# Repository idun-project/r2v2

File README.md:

## R2V2 - Dual-video switcher & converter for the Commodore 128

This is an open-source project that aims to improve the quality, flexibility, and convenience of the dual-video outputs of the Commodore 128.

In the normal configuration, the C128 has two independent video outputs for the VDC (80-column mode) and the VIC-II (40-column mode) displays. Each display requires its own cable going to its own specific type of monitor input, with the ideal being RGBI input for the 80col display and S-video for the 40col display. You can use two monitors, or you can use a retro monitor (e.g. Commodore 1084) that is manually switchable between two inputs.

With R2V2 installed in a C128, a single port, cable, and monitor input is used for BOTH display modes AND the display mode is switchable using the keyboard or with software control. If you also have the [idun-cartridge](https://github.com/idun-project/idun-cartridge), its software will be able to switch the displays automatically.

### Components

VDC Enhancer (8568) front

VDC Enhancer (8563) back

R2V2 requires two small PCBs installed internally. One sits under the VDC chip, and can optionally include 64KB video RAM expanasion. There are versions for the MOS8563 and the MOS8568 (for C128-DCR). The second PCB installed is from the breakable PCB pictured and is either:

1. An RF modulator replacement, which enhances the 8-pin DIN monitor port plus adds composite monitor and stereo audio outputs (supports 2 SIDs). It can also support switchable **HDMI OUT** from the composite port! (Requires additional components)
2. A modification for the DB-9 monitor port, which outputs analog RGB (rather than RGBI) and can also be used for switchable **HDMI OUT**.

### Status

This is an open-source project still in the R&D phase. It is not fully baked, and you should not try to build it _unless you want to contribute to the testing/debugging effort_.

- [x] Prototype PCBs manufactured
    - [x] MOS8568 VDC enhancer
    - [x] MOS8563 VDC enhancer
    - [x] analog board
- [ ] Prototype PCBs assembled
    - [ ] MOS8568 VDC enhancer
    - [ ] MOS8563 VDC enhancer w/o SRAM
    - [ ] MOS8563 VDC enhancer w/ SRAM
    - [ ] RF modulator replacement
    - [ ] DB-9 mod
- [ ] Testing
    - [ ] MOS8568+RF mod S-vid, composite, audio
    - [ ] MOS8563+RF mod S-vid, composite, audio
    - [ ] MOS8563+SRAM
    - [ ] MOS8563+RF mod LumaCode, mono-80c to RGBtoHDMI
    - [ ] MOS8568+DB-9 mod analog RGB
    - [ ] MOS8568+DB-9 mod LumaCode, color-80c to RGBtoHDMI
    - [ ] MOS8563+DB-9 mod LumaCode, color-80c to RGBtoHDMI

### Configurations

Many different configurations are possible, and depends on the kind of monitor you want to use, be it a retro CRT, modern monitor with analog input, or HDMI.

#### For analog monitor inputs

If you intend to use a monitor that supports S-video, you should be able to get good quality color output for both 80col and 40col display modes. Install the VDC enhancer compatible to your system and the RF modulator replacement, then connect the DIN monitor port to your display. You can use the audio on the DIN port, or plug in to the 3.5mm headphone jack.

If you intend to use a monitor that supports composite, you can get decent color 40col and monochrome 80col from the output on the RCA jack. Install the VDC enhancer and the RF modulator replacement, then connect the composite output to your display. Most likely, you will want to use the 3.5mm heahphone jack for audio.

It is possible to install both the RF modulator replacement and the DB-9 mod. If you do this, then you'll have analog RGB (both RGBS and RGBHV) on the DB-9, and that might be what you want for some monitors (e.g. SCART input). You'll have to work out your own switching between displays using this configuration.

#### For digital HDMI monitors

For the absolute best picture quality on modern displays, the R2V2 is combined with the [VIC-II LumaCode](https://github.com/c0pperdragon/LumaCode/wiki/VICIIdizer128-(for-the-C128)) enhancement and an external [RGBtoHDMI](https://github.com/hoglet67/RGBtoHDMI/wiki) video converter/upscaler.

There is a simpler version of the RGBtoHDMI designed by "C0pperdragon" that handles only LumaCode and monochrome video. This version can be used with the composite output on the RF modulator replacement. You will get color 40col and monochrome 80col display modes from a single HDMI input.

If you want the best HDMI experience with color 80col, then you'll need the more sophisticated RGBtoHDMI converter that handles both LumaCode and RGBS. This version connects with a custom cable to the DB-9 port and uses LumaCode for 40col mode and RGBS for 80col mode.

_NOTE_: A firmware patch and profile for the RGBtoHDMI is being developed so that it will automatically switch display modes as your C128 switches between 40/80col modes.

#### 64KB video RAM

The C128-DCR uses a MOS8568 VDC and came with 64KB of VRAM. Just use the MOS8568 version VDC enhancer and you're all set.

Other models of the C128 use a MOS8563 VDC and came with 16KB of VRAM. You must use the MOS8563 version VDC enhancer, and you can _optionally_ install 2 chips on the back of the PCB to upgrade to 64KB of VRAM.

### Build Instructions

TO BE CONTINUED...

### Installation Instructions

TO BE CONTINUED...

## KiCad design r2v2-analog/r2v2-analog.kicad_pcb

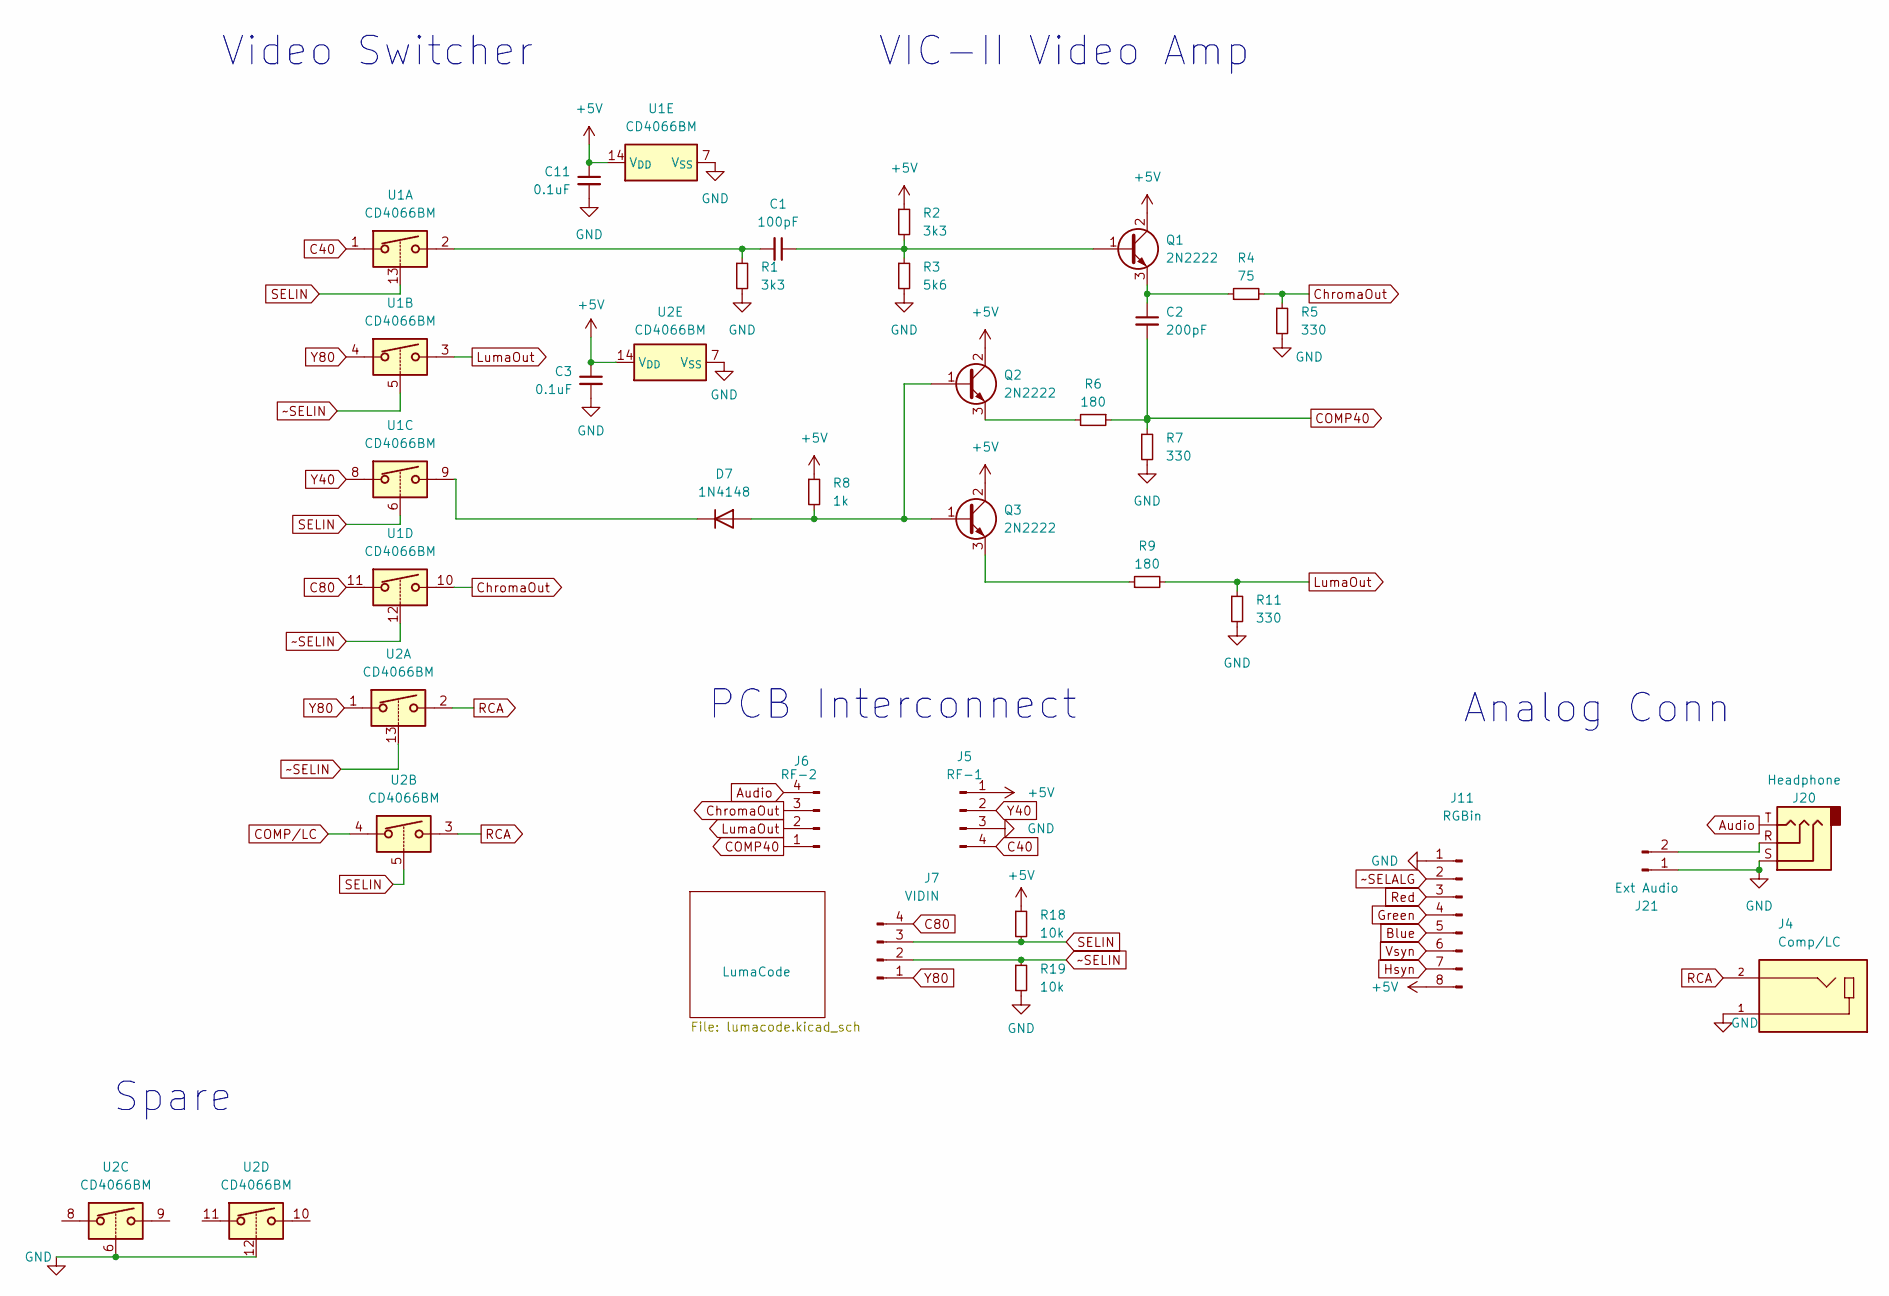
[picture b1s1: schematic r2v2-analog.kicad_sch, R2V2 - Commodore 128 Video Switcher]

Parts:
C1: 100pF; C_1206_3216Metric
C2: 200pF; C_1206_3216Metric
C3, C11: 0.1uF; C_1206_3216Metric
D7: 1N4148; D_SOD-123
J4: Comp/LC; CUI_RCJ-044; PARTREV 1.02
J5: RF-1; PinHeader_1x04_P2.54mm_Vertical
J6: RF-2; PinHeader_1x04_P2.54mm_Vertical
J7: VIDIN; PinHeader_1x04_P2.54mm_Vertical
J11: RGBin; PinHeader_2x04_P2.54mm_Vertical
J20: Headphone; Jack_3.5mm_CUI_SJ1-3523N_Horizontal
J21: Ext Audio; PinHeader_1x02_P2.54mm_Vertical
Q1, Q2, Q3: 2N2222; TO-92
R1, R2: 3k3; R_1206_3216Metric
R3: 5k6; R_1206_3216Metric
R4: 75; R_1206_3216Metric
R5, R7, R11: 330; R_1206_3216Metric
R6, R9: 180; R_1206_3216Metric
R8: 1k; R_1206_3216Metric
R18, R19: 10k; R_1206_3216Metric
U1, U2: CD4066BM; SO-14_3.9x8.65mm_P1.27mm

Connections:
+5V: C3.1, C11.1, J5.1, J11.8, Q1.2 (C), Q2.2 (C), Q3.2 (C), R2.1, R8.1, R18.1, U1.14 (V_{DD}), U2.14 (V_{DD}); also elsewhere on the board
Audio: J6.4, J20.T
Blue: J11.5; also elsewhere on the board
C40: J5.4, U1.1
C80: J7.4, U1.11
COMP40: C2.2, J6.1, R6.1, R7.1; also elsewhere on the board
COMP/LC: U2.4; also elsewhere on the board
ChromaOut: J6.3, R4.2, R5.1, U1.10
GND: C3.2, C11.2, J4.1, J5.3, J11.1, J20.S, J21.1, R1.2, R3.2, R5.2, R7.2, R11.2, R19.2, U1.7 (V_{SS}), U2.6, U2.7 (V_{SS}), U2.12; also elsewhere on the board
Green: J11.4; also elsewhere on the board
Hsyn: J11.7; also elsewhere on the board
LumaOut: J6.2, R9.2, R11.1, U1.3
unnamed: C1.2, R1.1, U1.2
unnamed: D7.2 (A), Q2.1 (B), Q3.1 (B), R8.2
unnamed: D7.1 (K), U1.9
unnamed: J20.R, J21.2
unnamed: C1.1, Q1.1 (B), R2.2, R3.1
unnamed: C2.1, Q1.3 (E), R4.1
unnamed: Q2.3 (E), R6.2
unnamed: Q3.3 (E), R9.1
RCA: J4.2, U2.2, U2.3
Red: J11.3; also elsewhere on the board
SELIN: J7.3, R18.2, U1.6, U1.13, U2.5
Vsyn: J11.6; also elsewhere on the board
Y40: J5.2, U1.8
Y80: J7.1, U1.4, U2.1
~SELALG: J11.2; also elsewhere on the board
~SELIN: J7.2, R19.1, U1.5, U1.12, U2.13

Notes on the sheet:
Spare
VIC-II Video Amp
Video Switcher
Analog Conn
PCB Interconnect

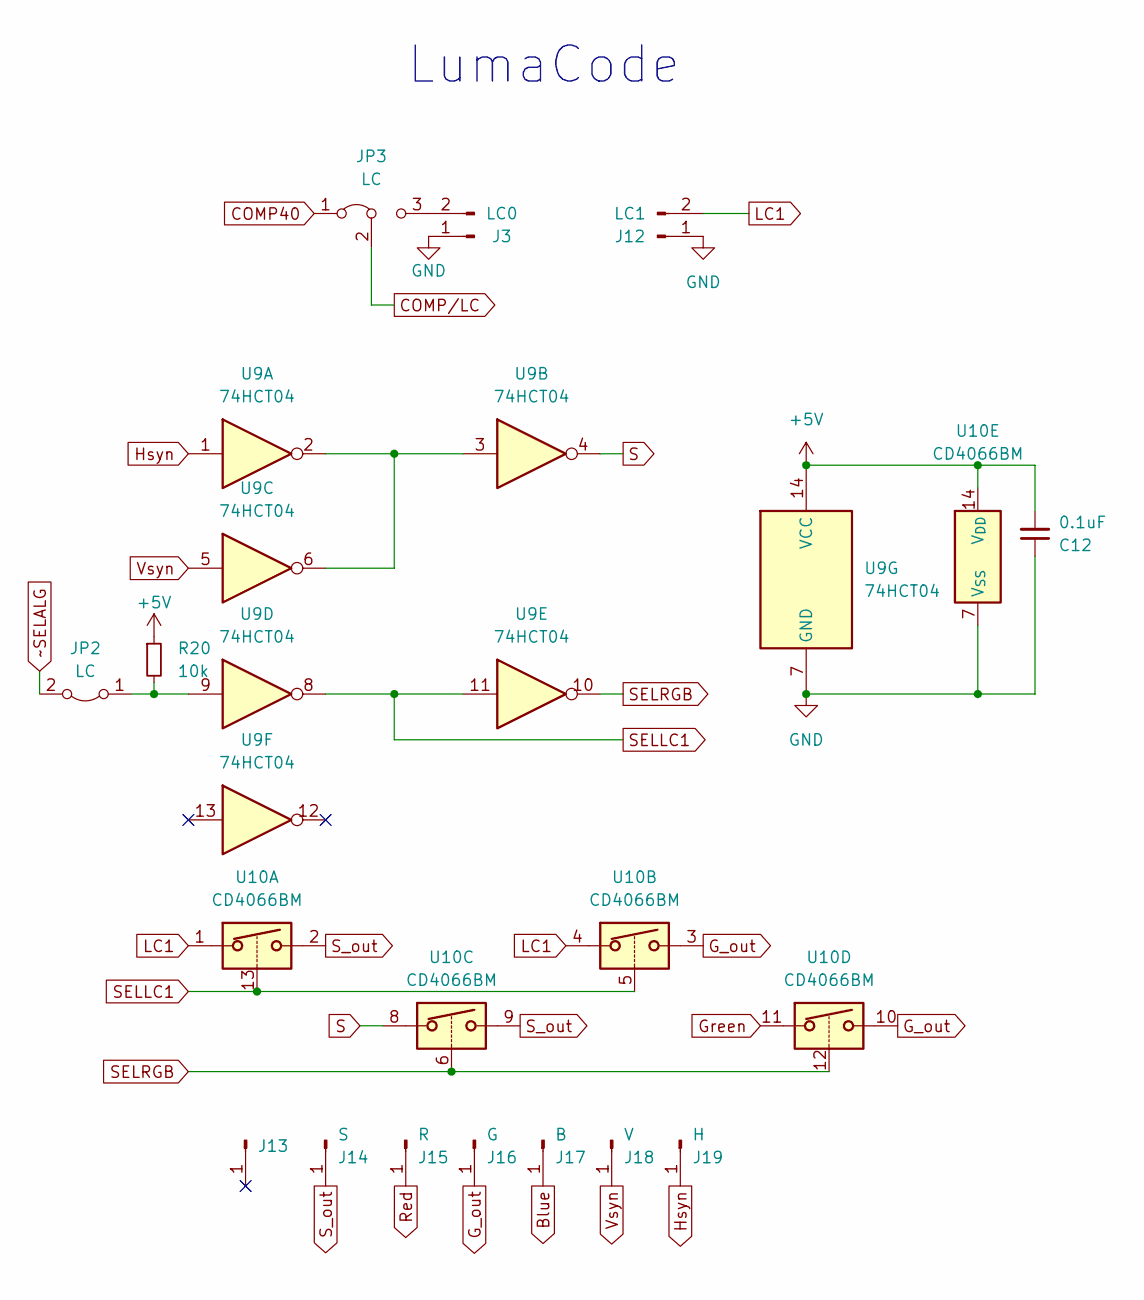
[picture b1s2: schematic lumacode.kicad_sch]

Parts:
C12: 0.1uF; C_1206_3216Metric
J3: LC0; PinHeader_1x02_P2.54mm_Vertical
J12: LC1; PinHeader_1x02_P2.54mm_Vertical
J13: PinHeader_1x01_P2.54mm_Vertical
J14: S; PinHeader_1x01_P2.54mm_Vertical
J15: R; PinHeader_1x01_P2.54mm_Vertical
J16: G; PinHeader_1x01_P2.54mm_Vertical
J17: B; PinHeader_1x01_P2.54mm_Vertical
J18: V; PinHeader_1x01_P2.54mm_Vertical
J19: H; PinHeader_1x01_P2.54mm_Vertical
JP2: LC; PinHeader_1x02_P1.27mm_Vertical
JP3: LC; PinHeader_1x03_P1.27mm_Vertical
R20: 10k; R_1206_3216Metric
U9: 74HCT04; SO-14_3.9x8.65mm_P1.27mm
U10: CD4066BM; SO-14_3.9x8.65mm_P1.27mm

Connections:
+5V: C12.2, R20.1, U9.14 (VCC), U10.14 (V_{DD}); also elsewhere on the board
Blue: J17.1; also elsewhere on the board
COMP40: JP3.1 (A); also elsewhere on the board
COMP/LC: JP3.2 (C); also elsewhere on the board
GND: C12.1, J3.1, J12.1, U9.7 (GND), U10.7 (V_{SS}); also elsewhere on the board
G_out: J16.1, U10.3, U10.10
Green: U10.11; also elsewhere on the board
Hsyn: J19.1, U9.1; also elsewhere on the board
LC1: J12.2, U10.1, U10.4
unnamed: J3.2, JP3.3 (B)
unnamed: JP2.1 (A), R20.2, U9.9
unnamed: U9.2, U9.3, U9.6
Red: J15.1; also elsewhere on the board
S: U9.4, U10.8
SELLC1: U9.8, U9.11, U10.5, U10.13
SELRGB: U9.10, U10.6, U10.12
S_out: J14.1, U10.2, U10.9
Vsyn: J18.1, U9.5; also elsewhere on the board
~SELALG: JP2.2 (B); also elsewhere on the board

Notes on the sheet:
LumaCode

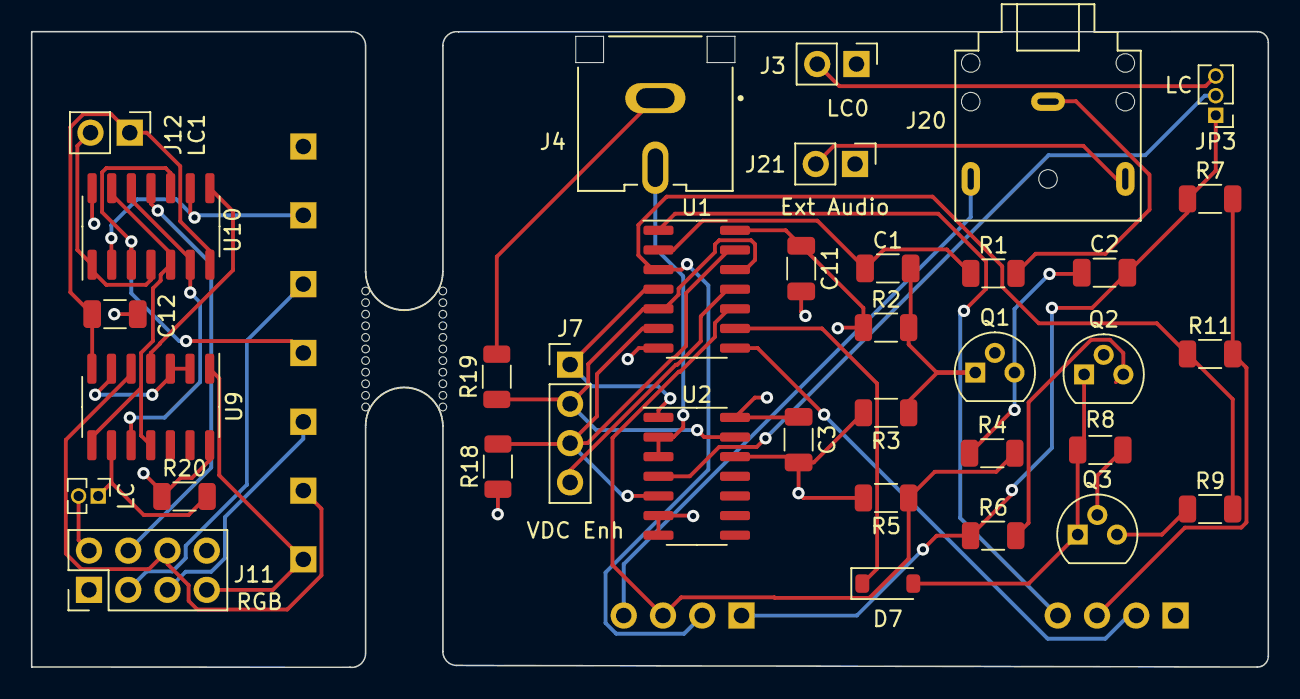
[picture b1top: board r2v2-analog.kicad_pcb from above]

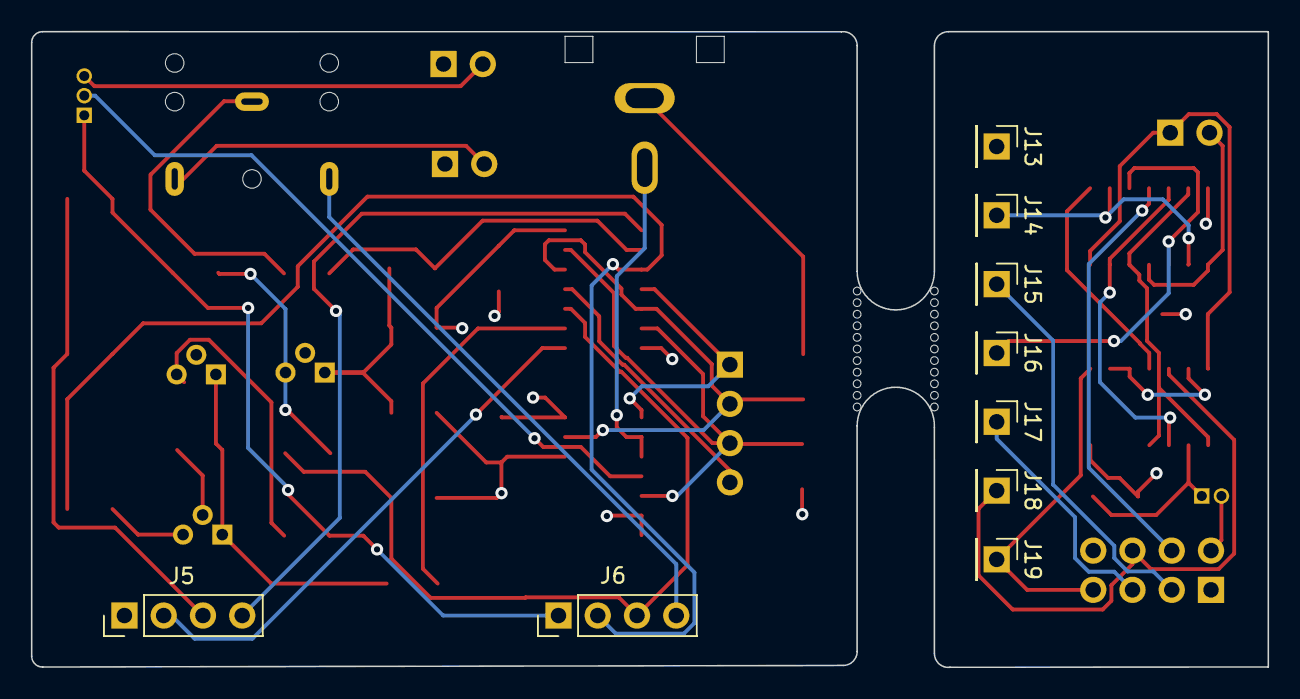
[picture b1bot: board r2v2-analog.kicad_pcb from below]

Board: 4 copper layers, 80.0 x 41.1 mm, 45 parts (9 on the bottom side), 37 nets.

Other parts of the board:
mouse-bite-5mm-slot: VAL**; mouse-bite-5mm-slot

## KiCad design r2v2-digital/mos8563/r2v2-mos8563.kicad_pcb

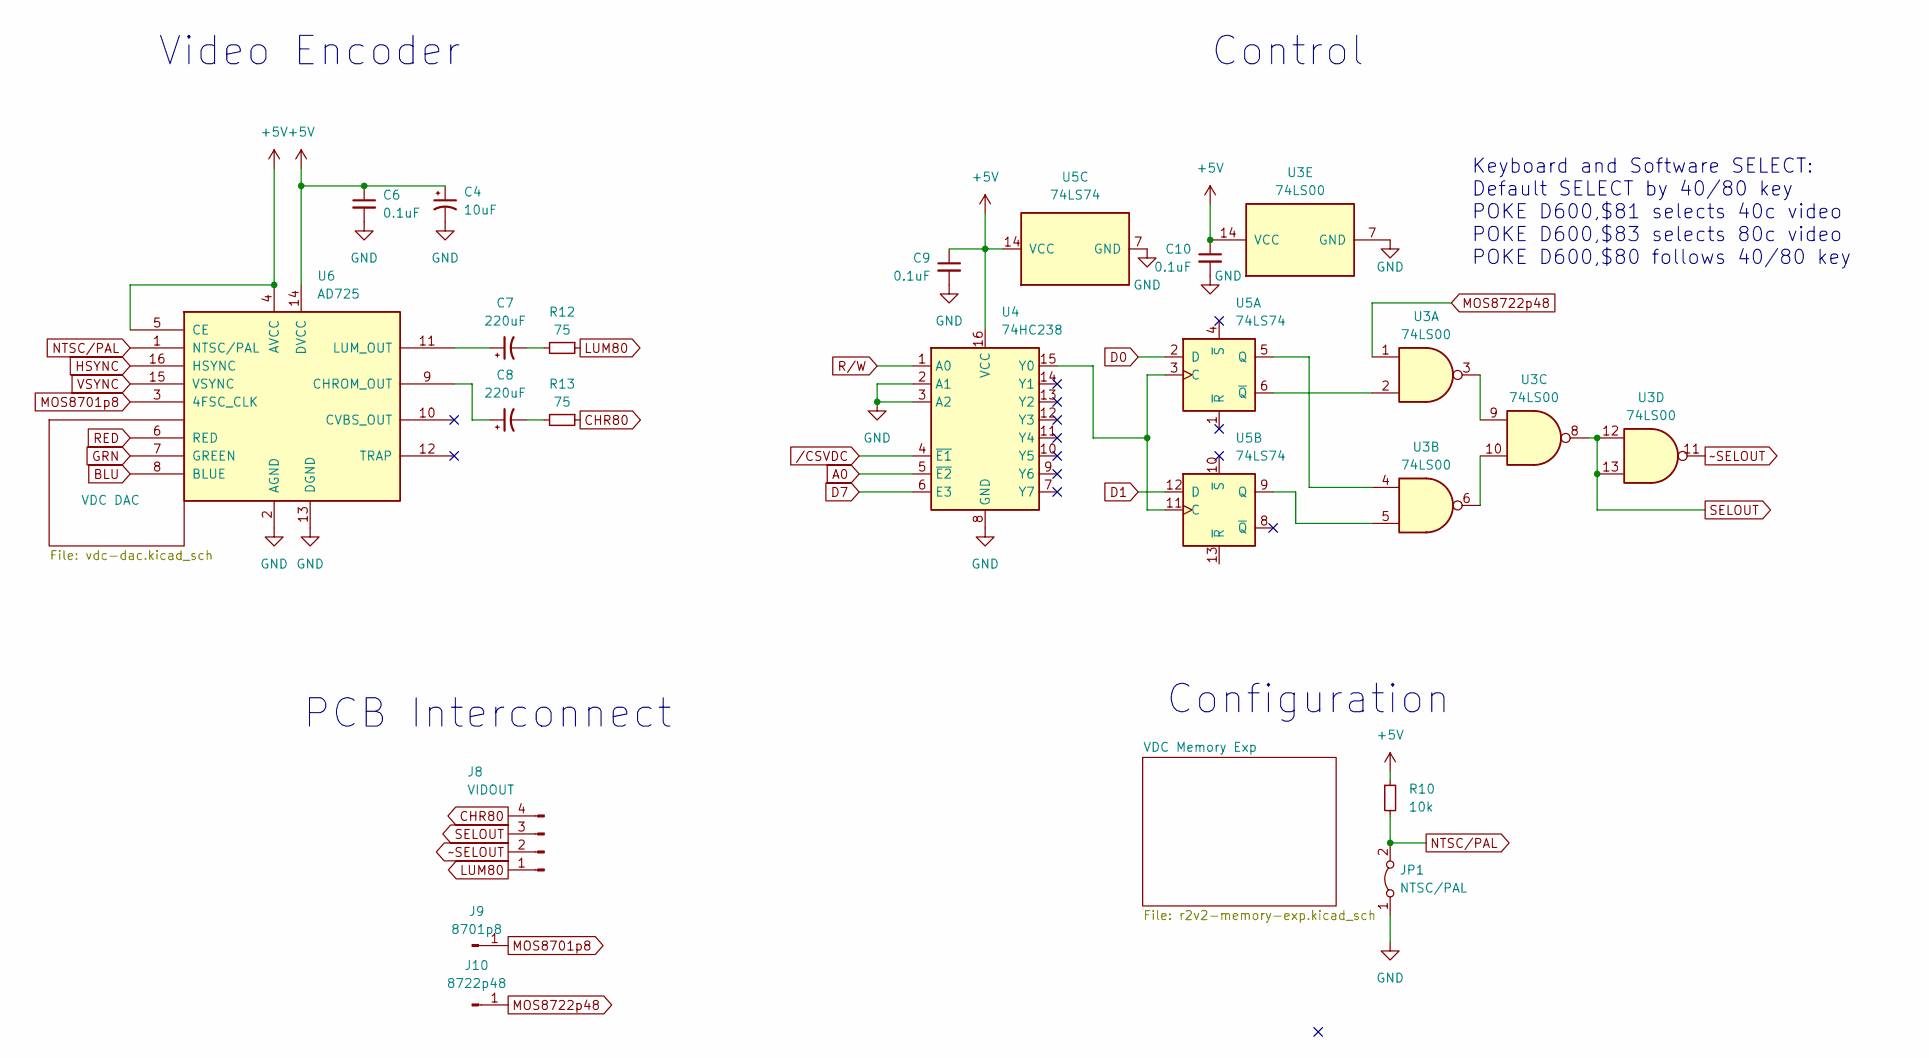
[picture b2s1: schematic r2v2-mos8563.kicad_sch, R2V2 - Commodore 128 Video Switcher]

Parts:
C4: 10uF; C_1206_3216Metric
C6, C9, C10: 0.1uF; C_1206_3216Metric
C7, C8: 220uF; C_1206_3216Metric
J8: VIDOUT; PinHeader_1x04_P2.54mm_Vertical
J9: 8701p8; PinHeader_1x01_P2.54mm_Vertical
J10: 8722p48; PinHeader_1x01_P2.54mm_Vertical
JP1: NTSC/PAL; PinHeader_1x02_P1.27mm_Vertical
R10: 10k; R_1206_3216Metric
R12, R13: 75; R_1206_3216Metric
U3: 74LS00; SOIC-14_3.9x8.7mm_P1.27mm
U4: 74HC238; SOIC-16_3.9x9.9mm_P1.27mm
U5: 74LS74; SO-14_3.9x8.65mm_P1.27mm
U6: AD725; SOIC-16W_7.5x10.3mm_P1.27mm

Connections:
+5V: C4.1, C6.1, C9.1, C10.1, R10.1, U3.14 (VCC), U4.16 (VCC), U5.14 (VCC), U6.4 (AVCC), U6.5 (CE), U6.14 (DVCC); also elsewhere on the board
A0: U4.5 (~E2); also elsewhere on the board
BLU: U6.8 (BLUE); also elsewhere on the board
CHR80: J8.4, R13.1
D0: U5.2 (D); also elsewhere on the board
D1: U5.12 (D); also elsewhere on the board
D7: U4.6 (E3)
GND: C4.2, C6.2, C9.2, C10.2, JP1.1 (A), U3.7 (GND), U4.2 (A1), U4.3 (A2), U4.8 (GND), U5.7 (GND), U6.2 (AGND), U6.13 (DGND); also elsewhere on the board
GRN: U6.7 (GREEN); also elsewhere on the board
HSYNC: U6.16 (HSYNC); also elsewhere on the board
LUM80: J8.1, R12.1
MOS8701p8: J9.1, U6.3 (4FSC_CLK)
MOS8722p48: J10.1, U3.1
NTSC/PAL: JP1.2 (B), R10.2, U6.1 (NTSC/PAL)
unnamed: C7.2, R12.2
unnamed: C8.2, R13.2
unnamed: U3.3, U3.9
unnamed: U3.6, U3.10
unnamed: U4.15 (Y0), U5.3 (C), U5.11 (C)
unnamed: U3.4, U5.5 (Q)
unnamed: U3.2, U5.6 (~Q)
unnamed: U3.5, U5.9 (Q)
unnamed: C8.1, U6.9 (CHROM_OUT)
unnamed: C7.1, U6.11 (LUM_OUT)
RED: U6.6 (RED); also elsewhere on the board
R/W: U4.1 (A0); also elsewhere on the board
SELOUT: J8.3, U3.8, U3.12, U3.13
VSYNC: U6.15 (VSYNC); also elsewhere on the board
/CSVDC: U4.4 (~E1); also elsewhere on the board
~SELOUT: J8.2, U3.11; also elsewhere on the board

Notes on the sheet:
Control
Video Encoder
Keyboard and Software SELECT: Default SELECT by 40/80 key POKE D600,$81 selects 40c video POKE D600,$83 selects 80c video POKE D600,$80 follows 40/80 key
Configuration
PCB Interconnect

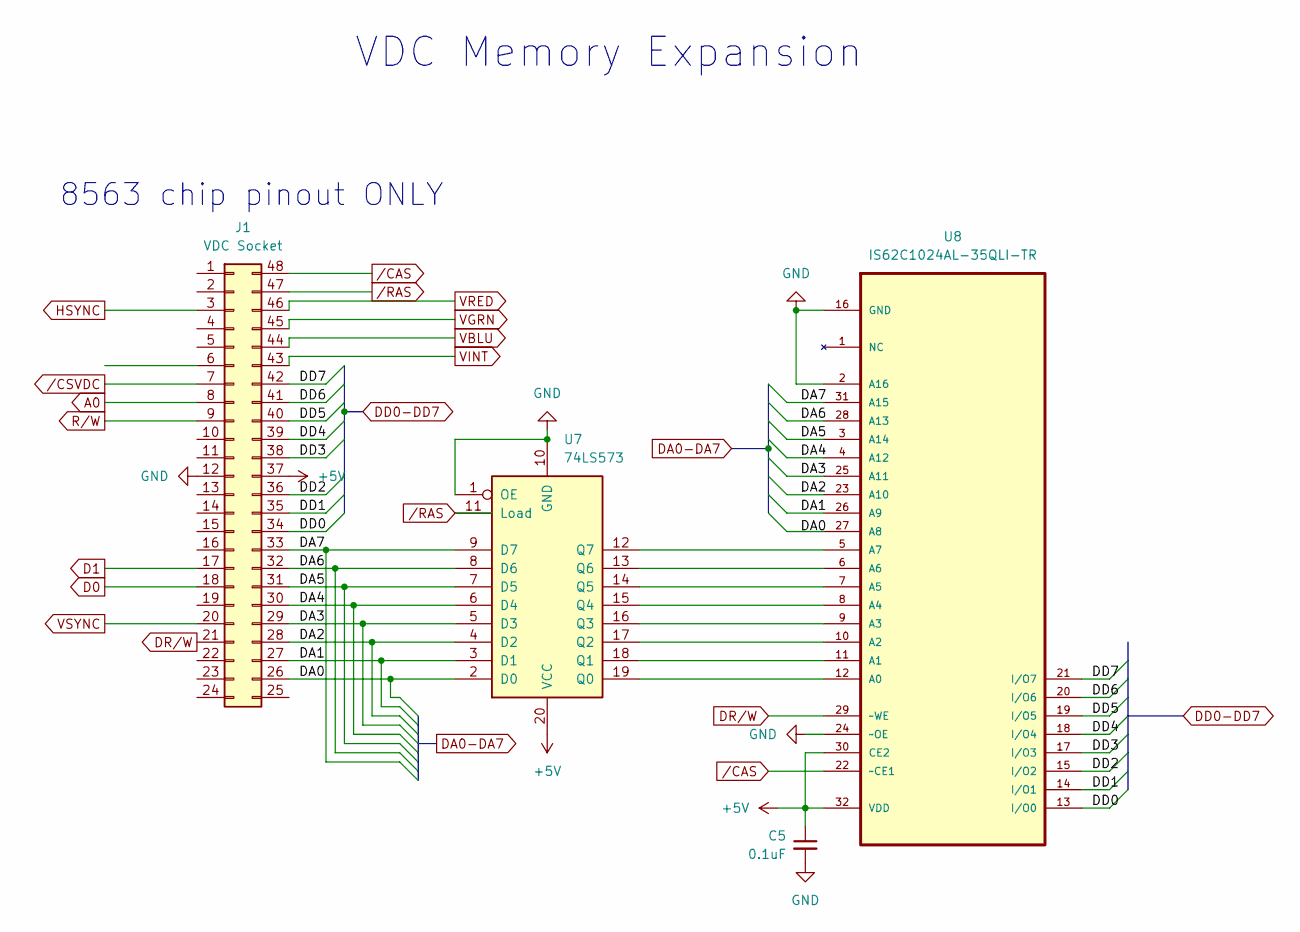
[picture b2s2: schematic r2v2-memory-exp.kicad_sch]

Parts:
C5: 0.1uF; C_1206_3216Metric
J1: VDC Socket; DIP-48_W15.24mm_Socket
U7: 74LS573; SOIC-20W_7.5x12.8mm_P1.27mm
U8: IS62C1024AL-35QLI-TR; SOIC127P1412X305-32N; MPN IS62C1024AL-35QLI-TR

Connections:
+5V: C5.1, J1.37, U7.20 (VCC), U8.30 (CE2), U8.32 (VDD); also elsewhere on the board
/VDC Memory Exp/DA0: J1.26, U7.2 (D0)
/VDC Memory Exp/DA1: J1.27, U7.3 (D1), U8.26 (A9)
/VDC Memory Exp/DA2: J1.28, U7.4 (D2), U8.23 (A10)
/VDC Memory Exp/DA3: J1.29, U7.5 (D3), U8.25 (A11)
/VDC Memory Exp/DA4: J1.30, U7.6 (D4), U8.4 (A12)
/VDC Memory Exp/DA5: J1.31, U7.7 (D5), U8.3 (A14)
/VDC Memory Exp/DA6: J1.32, U7.8 (D6), U8.28 (A13)
/VDC Memory Exp/DA7: J1.33, U7.9 (D7), U8.31 (A15)
/VDC Memory Exp/DD0: J1.34, U8.13 (I/O0)
/VDC Memory Exp/DD1: J1.35, U8.14 (I/O1)
/VDC Memory Exp/DD2: J1.36, U8.15 (I/O2)
/VDC Memory Exp/DD3: J1.38, U8.17 (I/O3)
/VDC Memory Exp/DD4: J1.39, U8.18 (I/O4)
/VDC Memory Exp/DD5: J1.40, U8.19 (I/O5)
/VDC Memory Exp/DD6: J1.41, U8.20 (I/O6)
/VDC Memory Exp/DD7: J1.42, U8.21 (I/O7)
A0: J1.8; also elsewhere on the board
D0: J1.18; also elsewhere on the board
D1: J1.17; also elsewhere on the board
DR/W: J1.21, U8.29 (~WE)
GND: C5.2, J1.12, U7.1 (OE), U7.10 (GND), U8.2 (A16), U8.16 (GND), U8.24 (~OE); also elsewhere on the board
HSYNC: J1.3; also elsewhere on the board
unnamed: U7.19 (Q0), U8.12 (A0)
unnamed: U7.18 (Q1), U8.11 (A1)
unnamed: U7.17 (Q2), U8.10 (A2)
unnamed: U7.16 (Q3), U8.9 (A3)
unnamed: U7.15 (Q4), U8.8 (A4)
unnamed: U7.14 (Q5), U8.7 (A5)
unnamed: U7.13 (Q6), U8.6 (A6)
unnamed: U7.12 (Q7), U8.5 (A7)
R/W: J1.9; also elsewhere on the board
VBLU: J1.44; also elsewhere on the board
VGRN: J1.45; also elsewhere on the board
VINT: J1.43; also elsewhere on the board
VRED: J1.46; also elsewhere on the board
VSYNC: J1.20; also elsewhere on the board
/CAS: J1.48, U8.22 (~CE1)
/CSVDC: J1.7; also elsewhere on the board
/RAS: J1.47, U7.11 (Load)

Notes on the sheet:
8563 chip pinout ONLY
VDC Memory Expansion

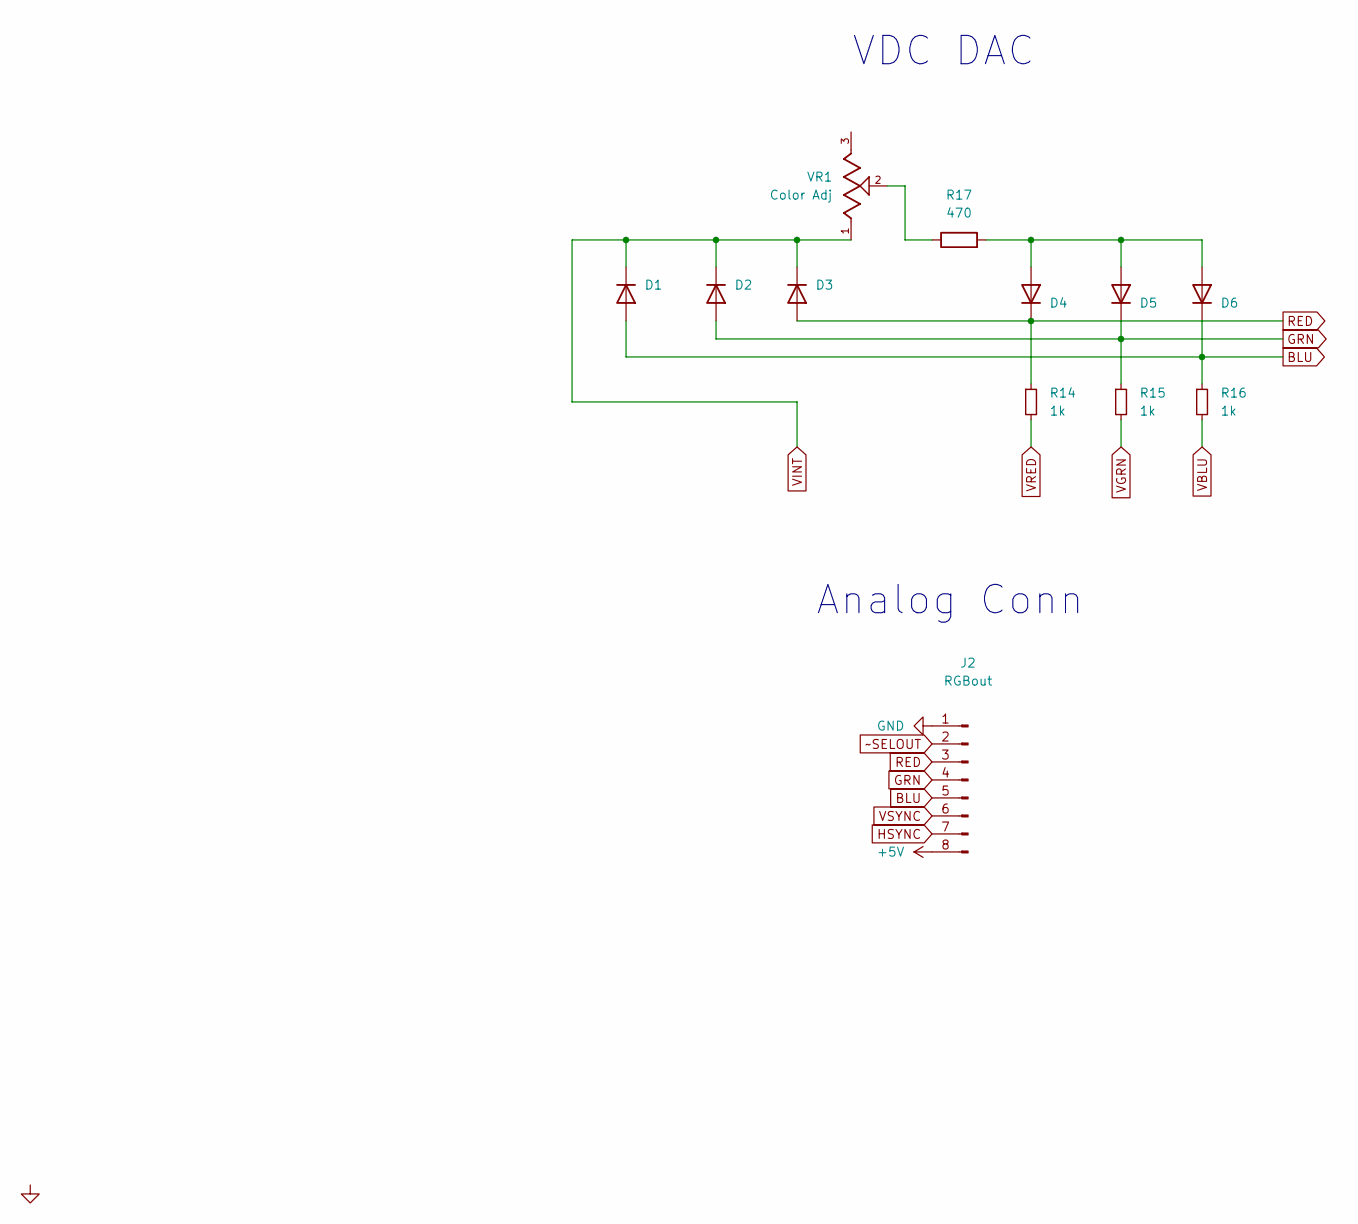
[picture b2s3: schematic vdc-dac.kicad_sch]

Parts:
D1, D2, D3, D4, D5, D6: 1N4148W; D_SOD-123
J2: RGBout; PinHeader_2x04_P2.54mm_Vertical
R14, R15, R16: 1k; R_1206_3216Metric
R17: 470; R_1206_3216Metric
VR1: Color Adj; TRIM_3314J-1-501E

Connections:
+5V: J2.8; also elsewhere on the board
BLU: D1.2 (A), D6.1 (K), J2.5, R16.1; also elsewhere on the board
GND: J2.1; also elsewhere on the board
GRN: D2.2 (A), D5.1 (K), J2.4, R15.1; also elsewhere on the board
HSYNC: J2.7; also elsewhere on the board
unnamed: D4.2 (A), D5.2 (A), D6.2 (A), R17.2
unnamed: R17.1, VR1.2
RED: D3.2 (A), D4.1 (K), J2.3, R14.1; also elsewhere on the board
VBLU: R16.2; also elsewhere on the board
VGRN: R15.2; also elsewhere on the board
VINT: D1.1 (K), D2.1 (K), D3.1 (K), VR1.1; also elsewhere on the board
VRED: R14.2; also elsewhere on the board
VSYNC: J2.6; also elsewhere on the board
~SELOUT: J2.2; also elsewhere on the board

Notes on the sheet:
VDC DAC
Analog Conn

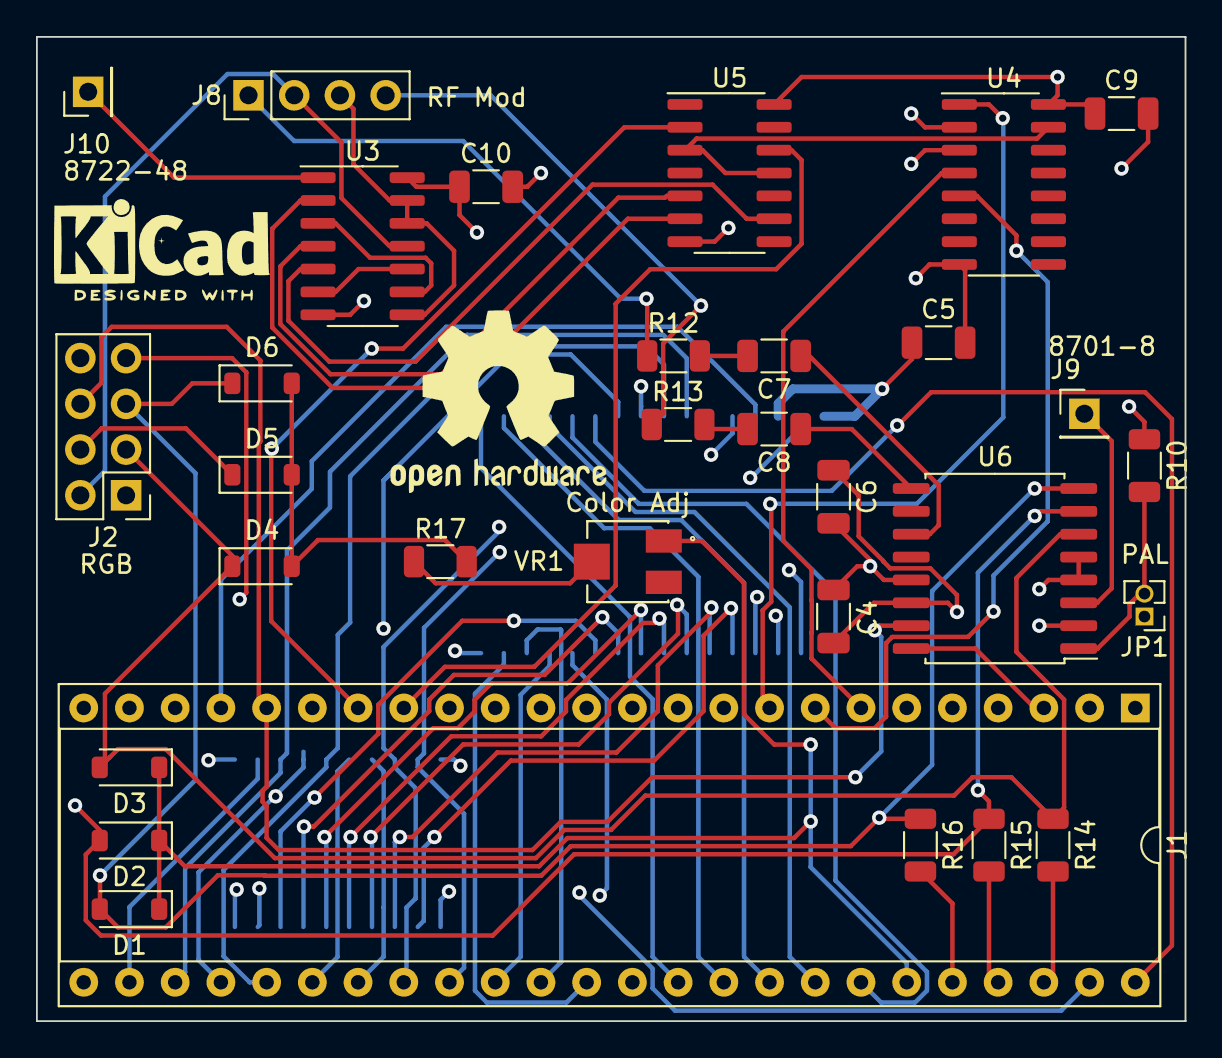
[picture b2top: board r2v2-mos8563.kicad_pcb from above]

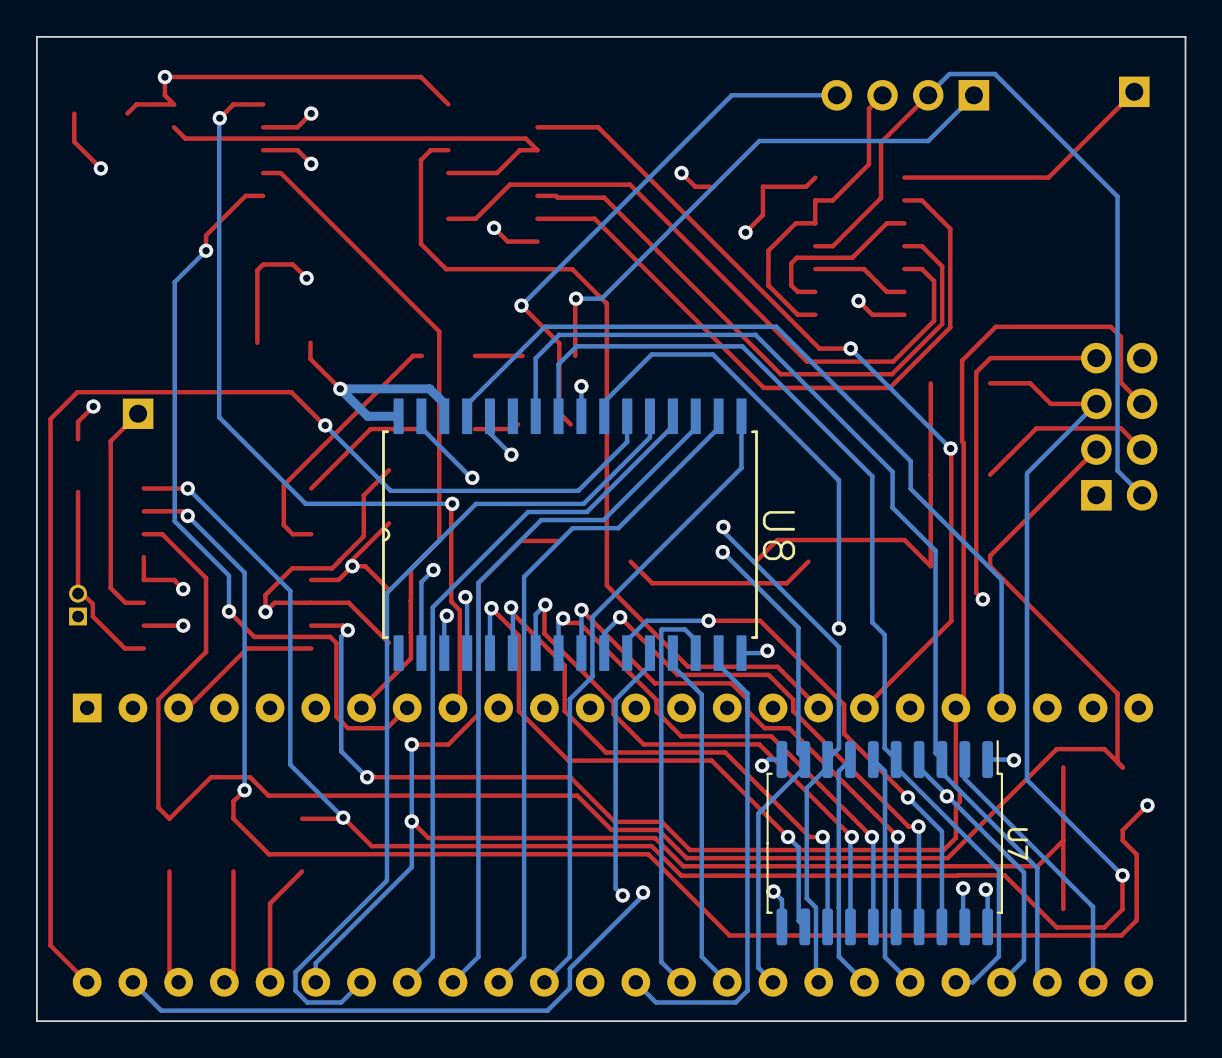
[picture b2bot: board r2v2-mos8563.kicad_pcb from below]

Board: 4 copper layers, 63.8 x 54.7 mm, 33 parts (2 on the bottom side), 62 nets.

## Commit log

2024-05-20 Added Creative Commons BY-SA 4.0 license file
2024-05-20 Minor README update
2024-05-21 Fixed typos in README

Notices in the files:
r2v2-analog/r2v2-analog.kicad_sch:
©2024 Brian Holdsworth
License CC-BY-SA 4.0
